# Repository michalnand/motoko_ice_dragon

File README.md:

# motoko ice dragon line follower

# source structure
- [3d_print](3d_print)
- [hardware](hardware)
- [simulations](simulations)
- [firmware](firmware)

# LQR controller 

## motor velocity control
- inner loop controls brushless motors
- LQR + Kalman are used for velocity control
- runs 4kHz

## position control
- outer loop controls robot state - distance and orientation
- LQR controller is used
- state is : (distance, orientation, velocity, angular rate)
- runs 250Hz

## LQR optimal control
- basic idea is solving discrete riccati algebraic equation
- to remove distrubance, integral action term is included

## motors velocity control
step response 1st order identification

- video of identification proces : https://www.youtube.com/watch?v=B-Wuzev6Ze0
- first the max RPM is estimated, using open loop and FOC controll
- during measuring max RPM the encoder noise variance is also measured (necessary for kalman filter)
- next step is calculating motor time constant (considering 1st order model)
- c++ source [identification.cpp](firmware/usr/identification.cpp#L16)
- LQR synthesis [lqg_discrete.ipynb](simulations/motor_controller/lqg_discrete.ipynb)
- step response and disturbance rejection

- controller for brushless motors in c++ (1D LQR + kalman) :
[lqg_single.cpp](firmware/LibsDrivers/lqg_single.cpp)

- whole motor driver : 
[motor_control.cpp](firmware/LibsDrivers/motor_control.cpp)

## position controll

- kalman based identification
- LQR synthesis
- [controller identification + synthetis](simulations/position_controller/position_controller_lqr.ipynb)
- step response and disturbance rejection

# photos

- [photos](doc/images/README.md)

- brushless motors
- LQG - linear quadratic regulator + Kalman filter
- LSTM for line shape prediction
- multiple local optimal LQR controllers selecting

# software architecture

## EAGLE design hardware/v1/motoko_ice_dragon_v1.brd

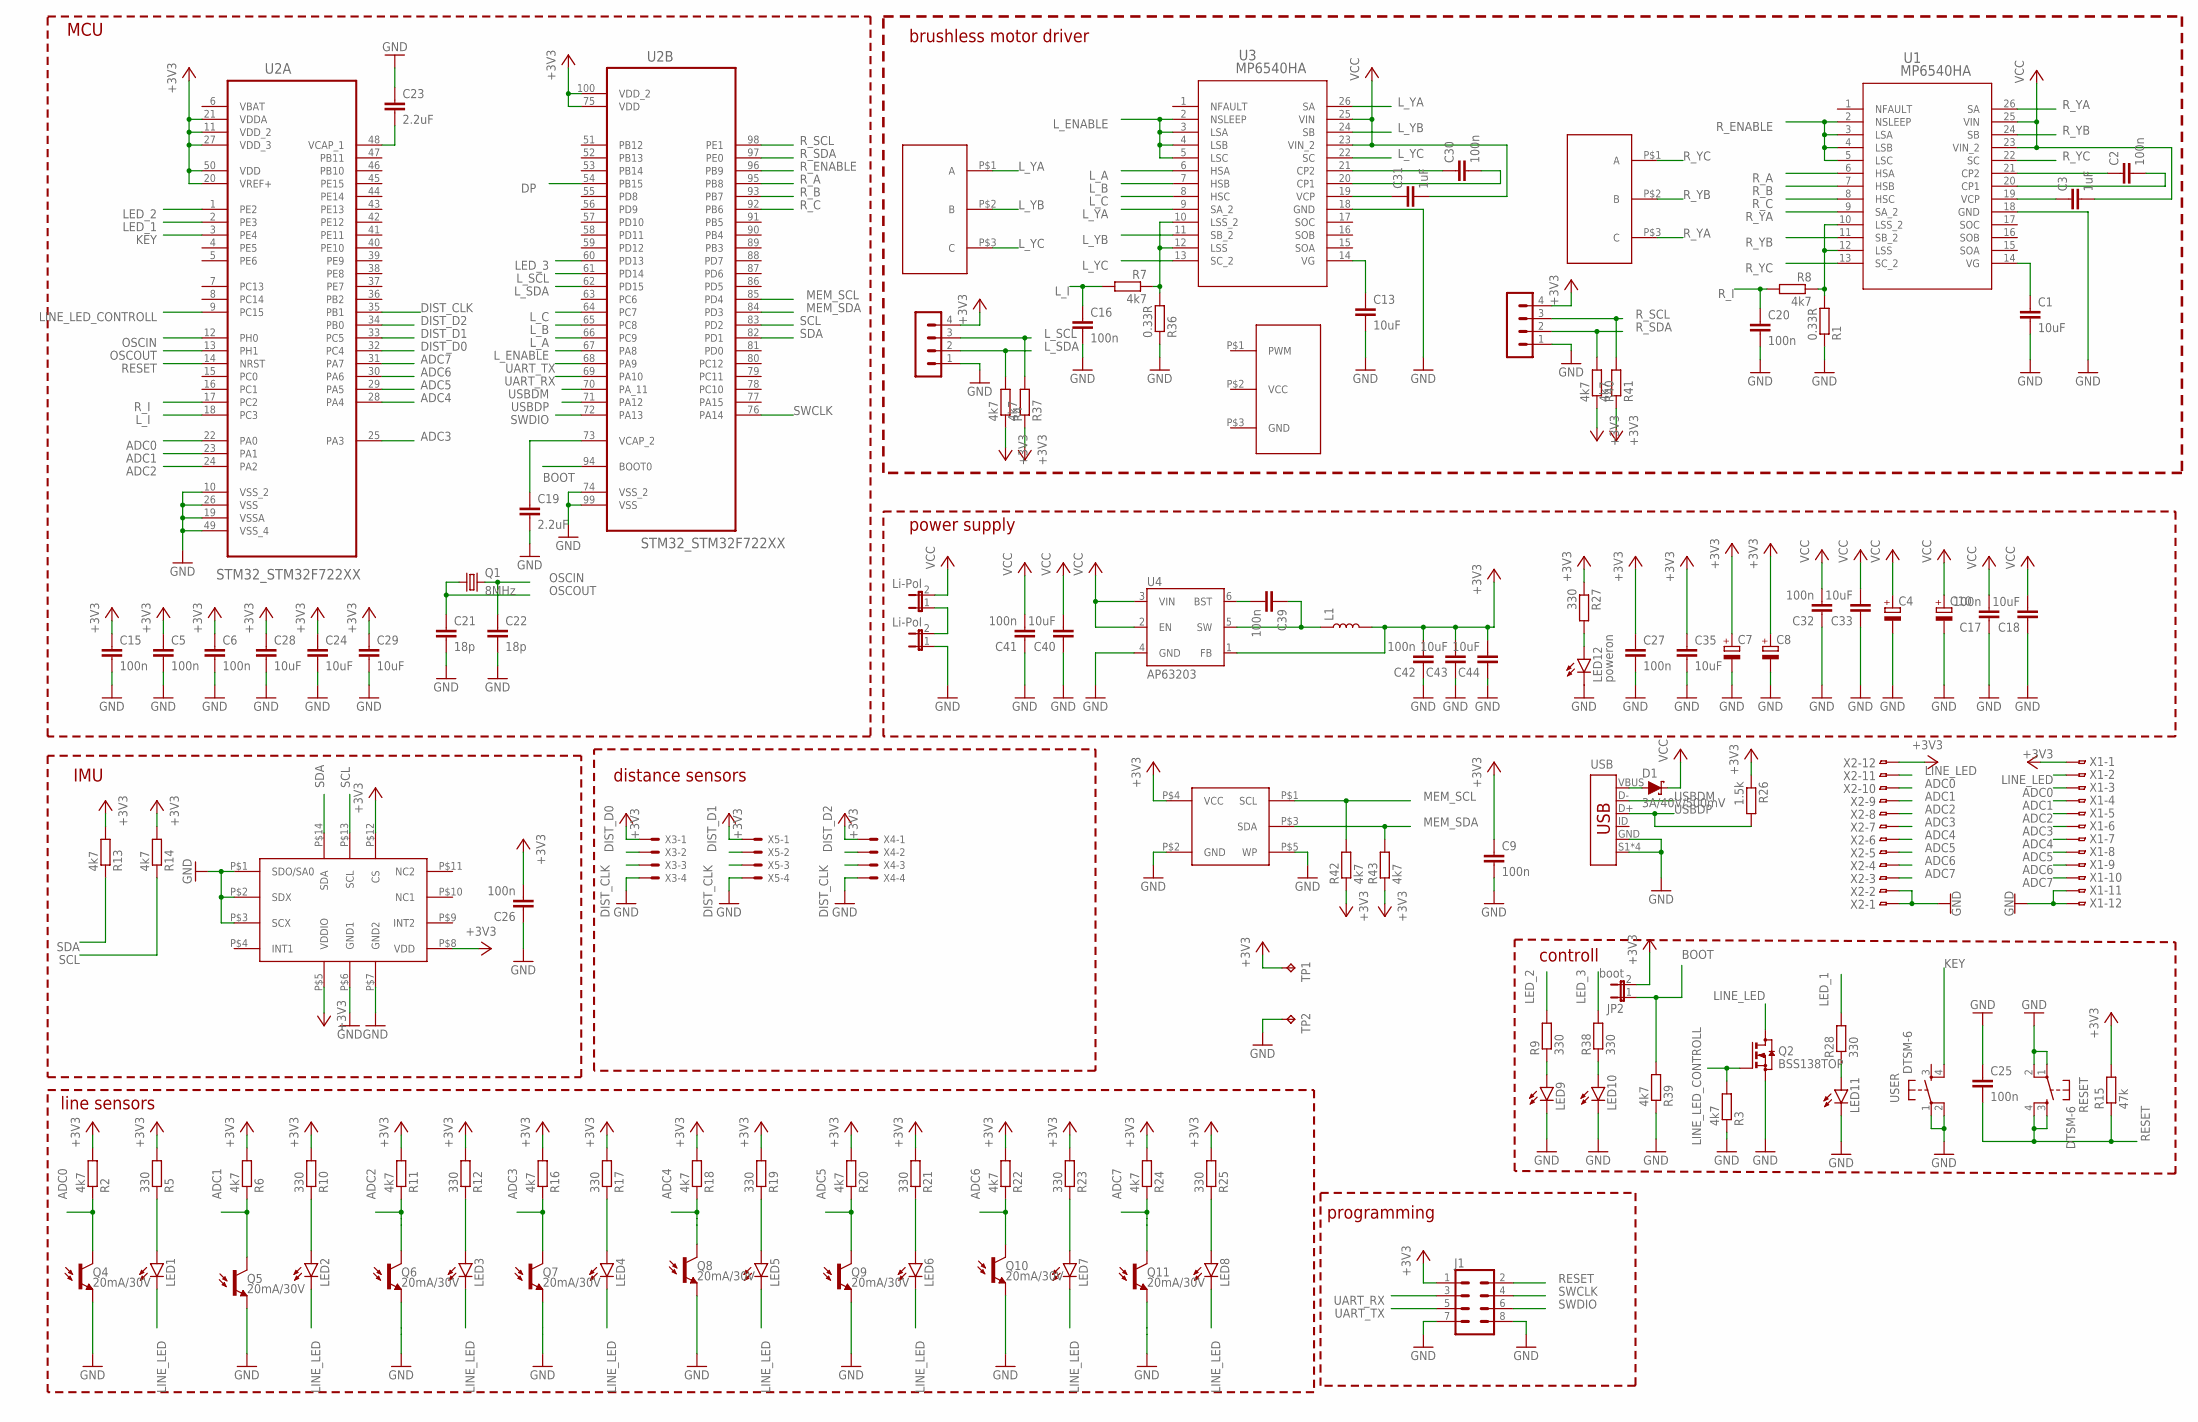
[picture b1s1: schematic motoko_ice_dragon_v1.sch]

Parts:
C1, C13, C18, C24, C28, C29, C33, C35, C40, C43, C44: 10uF; C0805
C2, C5, C6, C9, C15, C16, C17, C20, C25, C26, C27, C30, C32, C39, C41, C42: 100n; C0805
C3, C31: 1uF; C0805
C4, C7, C8, C10: CPOL-EU085CS-1AR; 085CS_1AR
C19, C23: 2.2uF; C0805
C21, C22: 18p; C0805
D1: 3A/40V/500mV; SMA-DIODE
J1: CONN_04X2; 2X4
JP1, JP3: Li-Pol; JP1
JP2: boot; JP1
L1: 4.7uH, TYS50204R7N-10; CR54
LED1, LED2, LED3, LED4, LED5, LED6, LED7, LED8, LED9, LED10, LED11: LEDCHIPLED_1206; CHIPLED_1206
LED12: poweron; CHIPLED_1206
L_ENCODER, L_ENCODER1: MA04-1
Q1: 8MHz; CTS406
Q2: BSS138TOP; SOT23
Q4, Q5, Q6, Q7, Q8, Q9, Q10, Q11: 20mA/30V; PT17-21C-L41-TR8
R1, R36: 0.33R; M1206
R2, R3, R4, R6, R7, R8, R11, R13, R14, R16, R18, R20, R22, R24, R37, R39, R40, R41, R42, R43: 4k7; M0805
R5, R9, R10, R12, R17, R19, R21, R23, R25, R27, R28, R38: 330; M0805
R15: 47k; M0805
R26: 1.5k; M0805
RESET: DTSM-6
TP1, TP2: TPB1,27; B1,27
U1, U3: MP6540HA; QFN-5X5_MP6540HA_MNP
U2: STM32_STM32F722XX; STM32_QFP50P1600X1600X160-100N
U4: AP63203; SOT23-6
U$1, U$2: BRUSHLESS_MOTOR_WHEEL
U$3: LSM6DSM; LGA14L
U$4: 24LC24_SOT23; SOT23
U$5: DUCTED_FAN_35MM
USB: USB_MINI-B_SMT; USB-MINIB
USER: DTSM-6
X1, X2: FH12-12S-0.5SH
X3, X4, X5: 52745-0490

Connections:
+3V3: C5.1, C6.1, C7.+, C8.+, C9.1, C15.1, C24.1, C26.2, C27.1, C28.1, C29.1, C35.1, C42.2, C43.2, C44.2, J1.1, JP2.2, L1.P$2 (2), L_ENCODER.4, L_ENCODER1.4, R2.2, R4.1, R5.2, R6.2, R10.2, R11.2, R12.2, R13.2, R14.2, R15.2, R16.2, R17.2, R18.2, R19.2, R20.2, R21.2, R22.2, R23.2, R24.2, R25.2, R26.1, R27.1, R37.1, R40.1, R41.1, R42.1, R43.1, TP1.TP, U2.11 (VDD_2), U2.20 (VREF+), U2.21 (VDDA), U2.27 (VDD_3), U2.50 (VDD), U2.75 (VDD), U2.100 (VDD_2), U4.1 (FB), U$3.P$5 (VDDIO), U$3.P$8 (VDD), U$3.P$12 (CS), U$4.P$4 (VCC), X1.1, X2.12, X3.1, X4.1, X5.1
ADC0: Q4.C, R2.1, U2.22 (PA0), X1.3, X2.10
ADC1: Q5.C, R6.1, U2.23 (PA1), X1.4, X2.9
ADC2: Q6.C, R11.1, U2.24 (PA2), X1.5, X2.8
ADC3: Q7.C, R16.1, U2.25 (PA3), X1.6, X2.7
ADC4: Q8.C, R18.1, U2.28 (PA4), X1.7, X2.6
ADC5: Q9.C, R20.1, U2.29 (PA5), X1.8, X2.5
ADC6: Q10.C, R22.1, U2.30 (PA6), X1.9, X2.4
ADC7: Q11.C, R24.1, U2.31 (PA7), X1.10, X2.3
BOOT: JP2.1, R39.2, U2.94 (BOOT0)
DIST_CLK: U2.35 (PB1), X3.3, X4.3, X5.3
DIST_D0: U2.32 (PC4), X3.2
DIST_D1: U2.33 (PC5), X5.2
DIST_D2: U2.34 (PB0), X4.2
DP: U2.54 (PB15)
GND: C1.2, C4.-, C5.2, C6.2, C7.-, C8.-, C9.2, C10.-, C13.2, C15.2, C16.2, C17.1, C18.1, C19.2, C20.2, C21.2, C22.2, C23.1, C24.2, C25.1, C26.1, C27.2, C28.2, C29.2, C32.1, C33.1, C35.2, C40.1, C41.1, C42.1, C43.1, C44.1, J1.7, J1.8, JP3.1, LED9.C, LED10.C, LED11.C, LED12.C, L_ENCODER.1, L_ENCODER1.1, Q2.2 (S), Q4.E, Q5.E, Q6.E, Q7.E, Q8.E, Q9.E, Q10.E, Q11.E, R1.1, R3.1, R36.1, R39.1, RESET.1, RESET.2, TP2.TP, U1.18 (GND), U2.10 (VSS_2), U2.19 (VSSA), U2.26 (VSS), U2.49 (VSS_4), U2.74 (VSS_2), U2.99 (VSS), U3.18 (GND), U4.4 (GND), U$3.P$1 (SDO/SA0), U$3.P$2 (SDX), U$3.P$3 (SCX), U$3.P$6 (GND1), U$3.P$7 (GND2), U$4.P$2 (GND), U$4.P$5 (WP), USB.GND, USB.S1 (SHIELD), USB.S2 (SHIELD), USB.S3 (SHIELD), USB.S4 (SHIELD), USER.1, USER.2, X1.11, X1.12, X2.1, X2.2, X3.4, X4.4, X5.4
KEY: U2.3 (PE4), USER.4
LED_1: R28.2, U2.2 (PE3)
LED_2: R9.2, U2.1 (PE2)
LED_3: R38.2, U2.60 (PD13)
LINE_LED: LED1.C, LED2.C, LED3.C, LED4.C, LED5.C, LED6.C, LED7.C, LED8.C, Q2.3 (D), X1.2, X2.11
LINE_LED_CONTROLL: Q2.1 (G), R3.2, U2.9 (PC15)
L_A: U2.66 (PC9), U3.6 (HSA)
L_B: U2.65 (PC8), U3.7 (HSB)
L_C: U2.64 (PC7), U3.8 (HSC)
L_ENABLE: U2.67 (PA8), U3.2 (NSLEEP), U3.3 (LSA), U3.4 (LSB), U3.5 (LSC)
L_I: C16.1, R7.2, U2.18 (PC3)
L_SCL: L_ENCODER.3, R37.2, U2.61 (PD14)
L_SDA: L_ENCODER.2, R4.2, U2.62 (PD15)
L_YA: U3.9 (SA_2), U3.26 (SA), U$1.P$1 (A)
L_YB: U3.11 (SB_2), U3.24 (SB), U$1.P$2 (B)
L_YC: U3.13 (SC_2), U3.22 (SC), U$1.P$3 (C)
MEM_SCL: R42.2, U2.85 (PD4), U$4.P$1 (SCL)
MEM_SDA: R43.2, U2.84 (PD3), U$4.P$3 (SDA)
unnamed: R7.1, R36.2, U3.10 (LSS_2), U3.12 (LSS)
unnamed: C1.1, U1.14 (VG)
unnamed: C2.1, U1.21 (CP2)
unnamed: C2.2, U1.20 (CP1)
unnamed: C3.1, U1.19 (VCP)
unnamed: D1.A, USB.VBUS
unnamed: JP1.1, JP3.2
unnamed: R1.2, R8.1, U1.10 (LSS_2), U1.12 (LSS)
unnamed: LED9.A, R9.1
unnamed: C13.1, U3.14 (VG)
unnamed: LED10.A, R38.1
unnamed: C31.1, U3.19 (VCP)
unnamed: LED1.A, R5.1
unnamed: LED2.A, R10.1
unnamed: LED3.A, R12.1
unnamed: LED4.A, R17.1
unnamed: LED5.A, R19.1
unnamed: LED6.A, R21.1
unnamed: LED7.A, R23.1
unnamed: LED8.A, R25.1
unnamed: C39.2, U4.6 (BST)
unnamed: LED12.A, R27.2
unnamed: C19.1, U2.73 (VCAP_2)
unnamed: C39.1, L1.P$1 (1), U4.5 (SW)
unnamed: C23.2, U2.48 (VCAP_1)
unnamed: C30.1, U3.21 (CP2)
unnamed: LED11.A, R28.1
unnamed: C30.2, U3.20 (CP1)
OSCIN: C22.1, Q1.3 (2), U2.12 (PH0)
OSCOUT: C21.1, Q1.1, U2.13 (PH1)
RESET: C25.2, J1.2, R15.1, RESET.3, RESET.4, U2.14 (NRST)
R_A: U1.6 (HSA), U2.95 (PB8)
R_B: U1.7 (HSB), U2.93 (PB7)
R_C: U1.8 (HSC), U2.92 (PB6)
R_ENABLE: U1.2 (NSLEEP), U1.3 (LSA), U1.4 (LSB), U1.5 (LSC), U2.96 (PB9)
R_I: C20.1, R8.2, U2.17 (PC2)
R_SCL: L_ENCODER1.3, R41.2, U2.98 (PE1)
R_SDA: L_ENCODER1.2, R40.2, U2.97 (PE0)
R_YA: U1.9 (SA_2), U1.26 (SA), U$2.P$3 (C)
R_YB: U1.11 (SB_2), U1.24 (SB), U$2.P$2 (B)
R_YC: U1.13 (SC_2), U1.22 (SC), U$2.P$1 (A)
SCL: R14.1, U2.83 (PD2), U$3.P$13 (SCL)
SDA: R13.1, U2.82 (PD1), U$3.P$14 (SDA)
SWCLK: J1.4, U2.76 (PA14)
SWDIO: J1.6, U2.72 (PA13)
UART_RX: J1.3, U2.69 (PA10)
UART_TX: J1.5, U2.68 (PA9)
USBDM: U2.70 (PA_11), USB.D-
USBDP: R26.2, U2.71 (PA12), USB.D+
VBAT: U2.6 (VBAT)
VCC: C3.2, C4.+, C10.+, C17.2, C18.2, C31.2, C32.2, C33.2, C40.2, C41.2, D1.C, JP1.2, U1.23 (VIN_2), U1.25 (VIN), U3.23 (VIN_2), U3.25 (VIN), U4.2 (EN), U4.3 (VIN)

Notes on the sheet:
power supply
line sensors
programming
MCU
distance sensors
controll
IMU
brushless motor driver

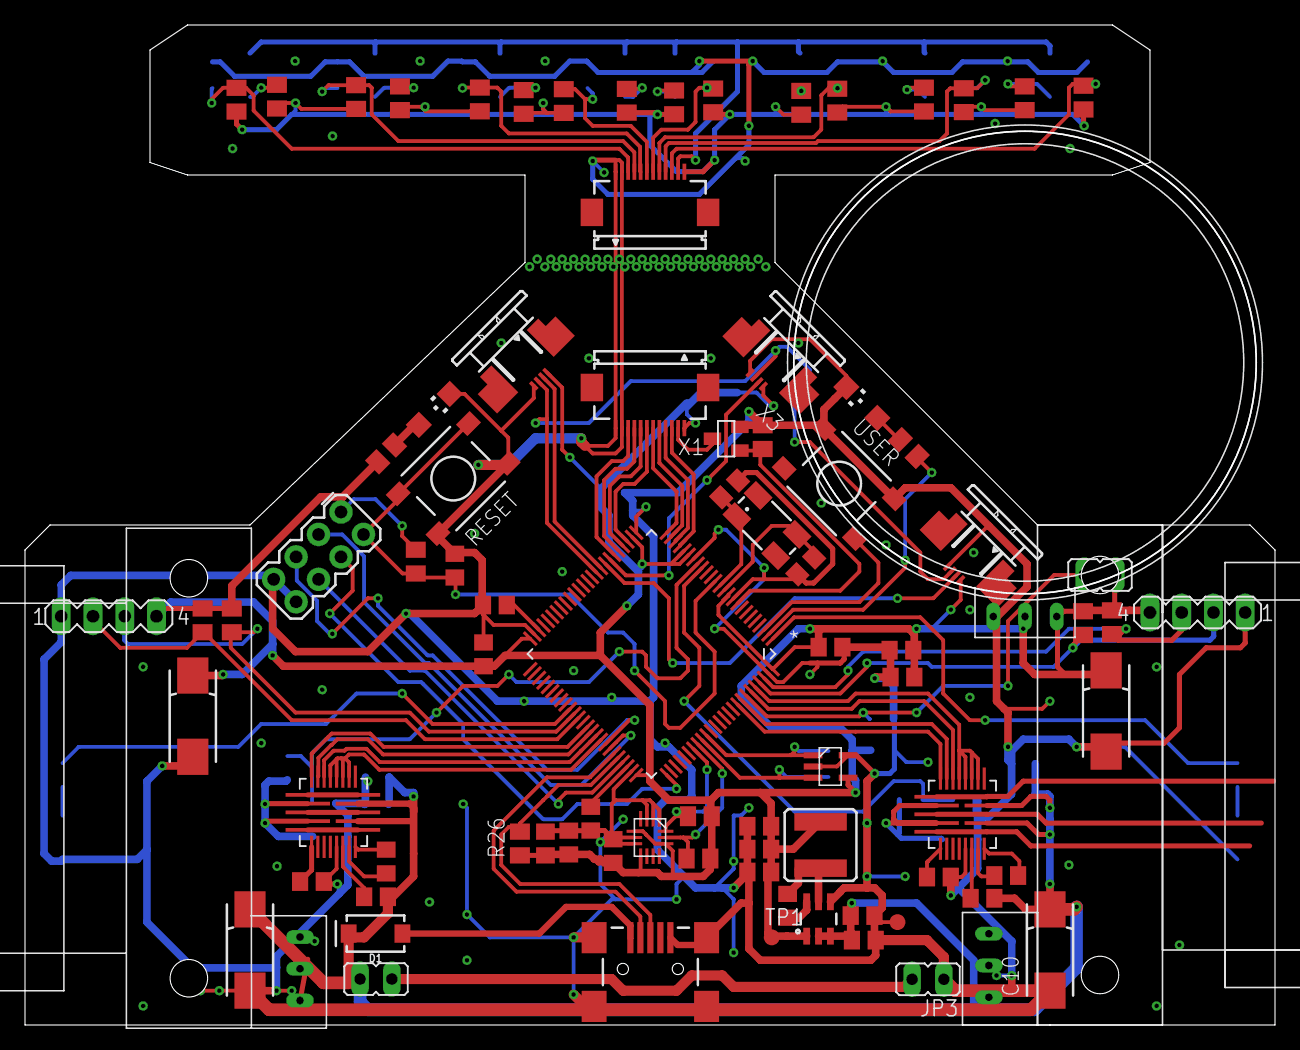
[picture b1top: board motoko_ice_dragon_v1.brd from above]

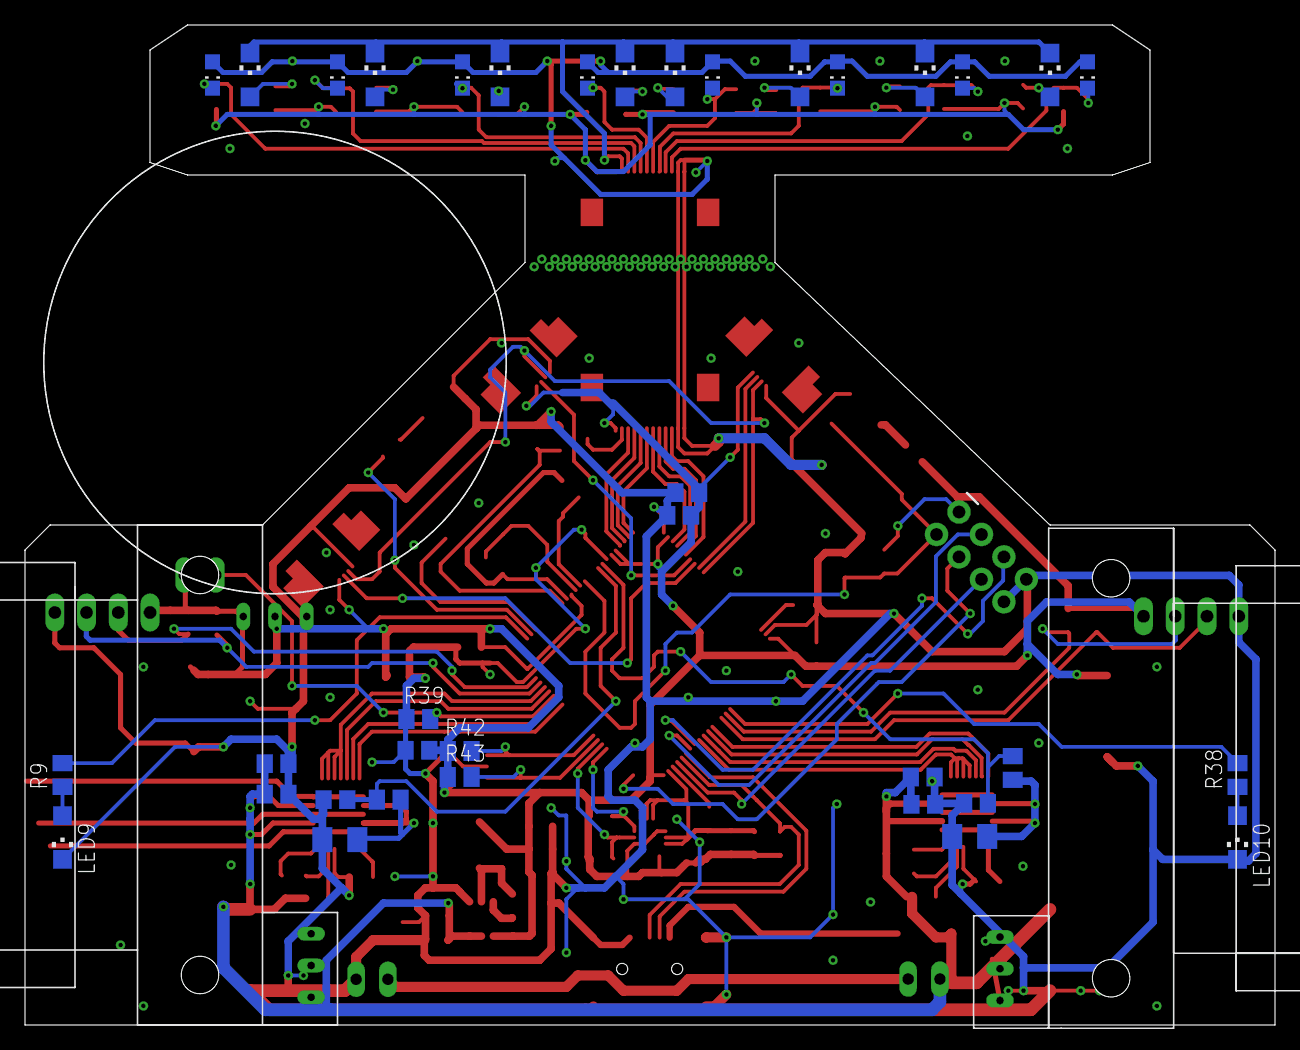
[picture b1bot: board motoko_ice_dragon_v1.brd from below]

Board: 2 copper layers, 100.0 x 80.0 mm, 122 parts (37 on the bottom side), 83 nets.

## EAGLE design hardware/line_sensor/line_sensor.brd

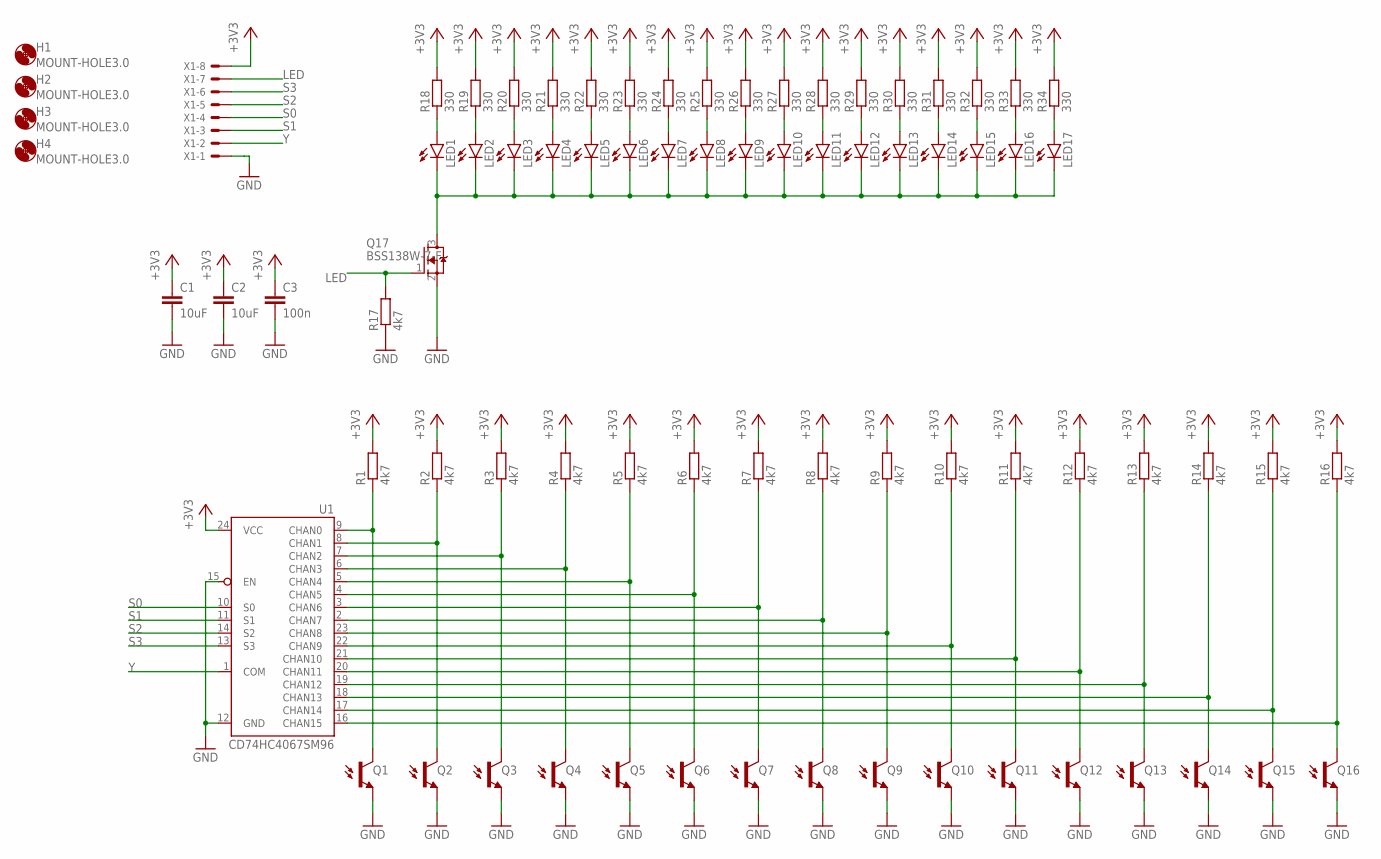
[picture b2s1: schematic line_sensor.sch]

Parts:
C1, C2: 10uF; C0805
C3: 100n; C0805
H1, H2, H3, H4: MOUNT-HOLE3.0; 3,0
LED1, LED2, LED3, LED4, LED5, LED6, LED7, LED8, LED9, LED10, LED11, LED12, LED13, LED14, LED15, LED16, LED17: LEDSML1206; SML1206
Q1, Q2, Q3, Q4, Q5, Q6, Q7, Q8, Q9, Q10, Q11, Q12, Q13, Q14, Q15, Q16: 20mA/30V; PT17-21C-L41-TR8
Q17: BSS138W-7-F; SOT323
R1, R2, R3, R4, R5, R6, R7, R8, R9, R10, R11, R12, R13, R14, R15, R16, R17: 4k7; M0805
R18, R19, R20, R21, R22, R23, R24, R25, R26, R27, R28, R29, R30, R31, R32, R33, R34: 330; M0805
U1: CD74HC4067SM96; SSOP24
X1: 52745-0890

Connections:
+3V3: C1.1, C2.1, C3.1, R1.2, R2.2, R3.2, R4.2, R5.2, R6.2, R7.2, R8.2, R9.2, R10.2, R11.2, R12.2, R13.2, R14.2, R15.2, R16.2, R18.2, R19.2, R20.2, R21.2, R22.2, R23.2, R24.2, R25.2, R26.2, R27.2, R28.2, R29.2, R30.2, R31.2, R32.2, R33.2, R34.2, U1.24 (VCC), X1.8
GND: C1.2, C2.2, C3.2, Q1.E, Q2.E, Q3.E, Q4.E, Q5.E, Q6.E, Q7.E, Q8.E, Q9.E, Q10.E, Q11.E, Q12.E, Q13.E, Q14.E, Q15.E, Q16.E, Q17.2 (S), R17.1, U1.12 (GND), U1.15 (EN), X1.1
LED: Q17.1 (G), R17.2, X1.7
unnamed: Q2.C, R2.1, U1.8 (CHAN1)
unnamed: Q1.C, R1.1, U1.9 (CHAN0)
unnamed: Q3.C, R3.1, U1.7 (CHAN2)
unnamed: Q4.C, R4.1, U1.6 (CHAN3)
unnamed: LED1.A, R18.1
unnamed: LED2.A, R19.1
unnamed: LED1.C, LED2.C, LED3.C, LED4.C, LED5.C, LED6.C, LED7.C, LED8.C, LED9.C, LED10.C, LED11.C, LED12.C, LED13.C, LED14.C, LED15.C, LED16.C, LED17.C, Q17.3 (D)
unnamed: Q5.C, R5.1, U1.5 (CHAN4)
unnamed: Q6.C, R6.1, U1.4 (CHAN5)
unnamed: Q7.C, R7.1, U1.3 (CHAN6)
unnamed: Q8.C, R8.1, U1.2 (CHAN7)
unnamed: Q9.C, R9.1, U1.23 (CHAN8)
unnamed: Q10.C, R10.1, U1.22 (CHAN9)
unnamed: Q11.C, R11.1, U1.21 (CHAN10)
unnamed: Q12.C, R12.1, U1.20 (CHAN11)
unnamed: Q13.C, R13.1, U1.19 (CHAN12)
unnamed: Q14.C, R14.1, U1.18 (CHAN13)
unnamed: Q15.C, R15.1, U1.17 (CHAN14)
unnamed: Q16.C, R16.1, U1.16 (CHAN15)
unnamed: LED3.A, R20.1
unnamed: LED4.A, R21.1
unnamed: LED5.A, R22.1
unnamed: LED6.A, R23.1
unnamed: LED7.A, R24.1
unnamed: LED8.A, R25.1
unnamed: LED9.A, R26.1
unnamed: LED10.A, R27.1
unnamed: LED11.A, R28.1
unnamed: LED12.A, R29.1
unnamed: LED13.A, R30.1
unnamed: LED14.A, R31.1
unnamed: LED15.A, R32.1
unnamed: LED16.A, R33.1
unnamed: LED17.A, R34.1
S0: U1.10 (S0), X1.4
S1: U1.11 (S1), X1.3
S2: U1.14 (S2), X1.5
S3: U1.13 (S3), X1.6
Y: U1.1 (COM), X1.2

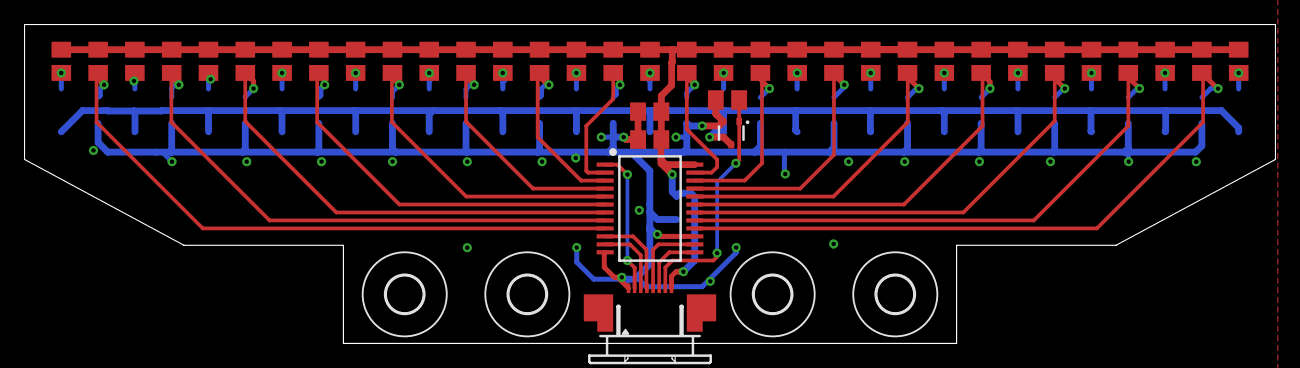
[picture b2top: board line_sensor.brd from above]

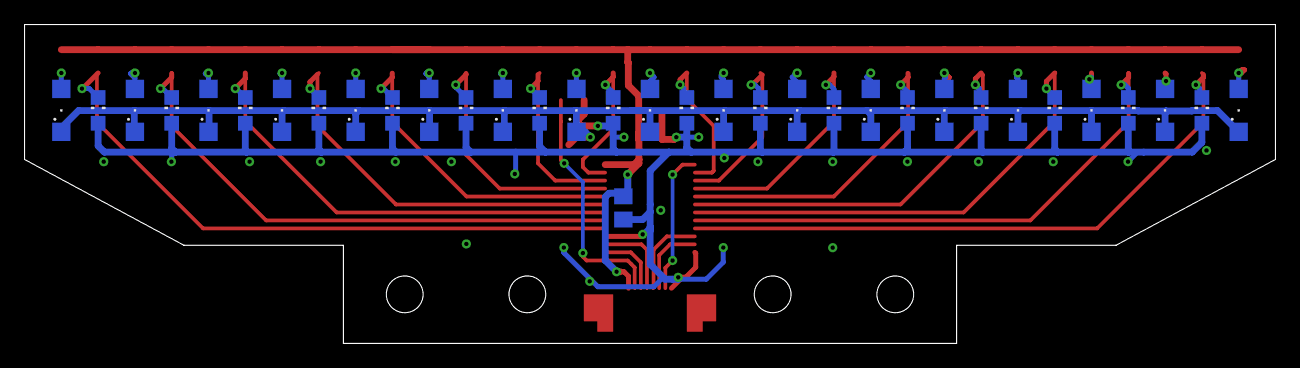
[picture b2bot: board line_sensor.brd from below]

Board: 2 copper layers, 102.0 x 26.0 mm, 77 parts (34 on the bottom side), 42 nets.

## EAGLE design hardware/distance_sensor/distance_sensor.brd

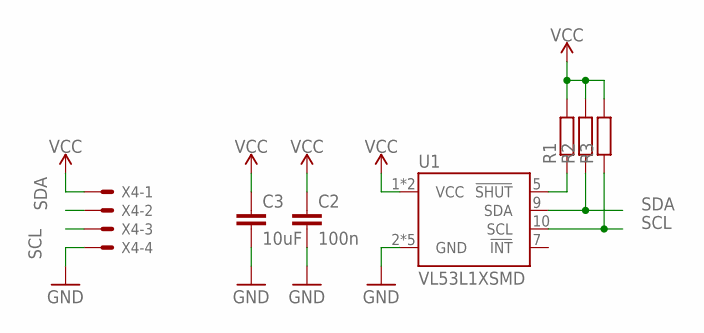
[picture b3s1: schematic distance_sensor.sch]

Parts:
C2: 100n; C0805
C3: 10uF; C0805
R1, R2, R3: R-EU_M0805; M0805
U1: VL53L1XSMD; VL53L1X
X4: 52745-0490

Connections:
GND: C2.2, C3.2, U1.2 (GND), U1.3 (GND), U1.4 (GND), U1.6 (GND), U1.12 (GND), X4.4
unnamed: R1.1, U1.5 (!SHUT)
SCL: R3.1, U1.10 (SCL), X4.3
SDA: R2.1, U1.9 (SDA), X4.2
VCC: C2.1, C3.1, R1.2, R2.2, R3.2, U1.1 (VCC), U1.11 (VCC), X4.1

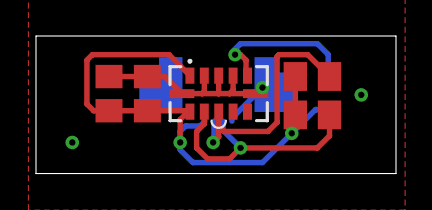
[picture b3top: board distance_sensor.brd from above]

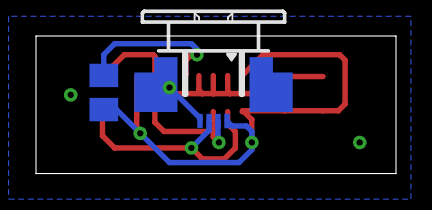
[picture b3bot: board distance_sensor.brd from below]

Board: 2 copper layers, 20.0 x 7.6 mm, 7 parts (2 on the bottom side), 5 nets.

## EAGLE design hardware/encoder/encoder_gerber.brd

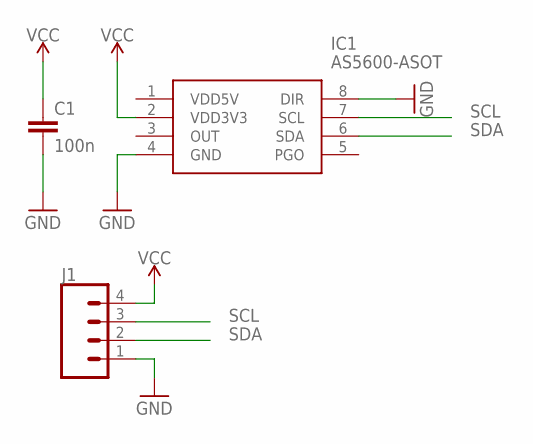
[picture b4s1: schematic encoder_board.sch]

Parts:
C1: 100n; C0805
IC1: AS5600-ASOT; SOIC127P600X175-8N
J1: CONN_04LONGPADS; 1X04_LONGPADS

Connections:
GND: C1.2, IC1.4 (GND), IC1.8 (DIR), J1.1
SCL: IC1.7 (SCL), J1.3
SDA: IC1.6 (SDA), J1.2
VCC: C1.1, IC1.2 (VDD3V3), J1.4

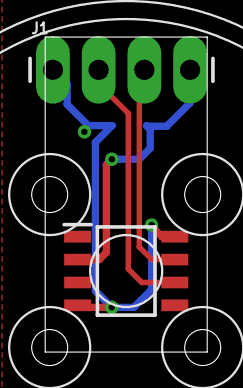
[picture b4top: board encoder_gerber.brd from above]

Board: 2 copper layers, 9.0 x 17.5 mm, 4 parts (1 on the bottom side), 4 nets.

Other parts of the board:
U$1: BRUSHLESS_GIMBAL_MOTOR_2204

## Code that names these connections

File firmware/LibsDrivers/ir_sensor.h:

#ifndef _IR_SENSOR_H_
#define _IR_SENSOR_H_

#include <gpio.h>
#include <biquad_filter.h>

#define IR_SENSORS_COUNT        ((unsigned int)4)


/*
    IR left         :   PB1     ADC1, ADC2, IN9
    IR front left   :   PC5     ADC1, ADC2, IN15
    IR front right  :   PC4     ADC1, ADC2, IN14
    IR right        :   PB0     ADC1, ADC2, IN8
*/

class IRSensor
{
    public:
        void init();

        void callback();

        float* get();

        int obstacle_detected();


        void print();
    
    private:
        float calibration(float *callibration, float x);

    public:
        uint32_t measurement_id;

    private: 
        uint32_t state;
        Gpio<TGPIOC, 14, GPIO_MODE_OUT> ir_led;         //ir led
  

        int ir_off[IR_SENSORS_COUNT];
        int ir_on[IR_SENSORS_COUNT];

        float filter_coeff;
        

    private:
        float distance[IR_SENSORS_COUNT];

};

#endif

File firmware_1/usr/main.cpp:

#include "device.h"
#include <drivers.h>
#include <tests.h>

#include <identification.h>
#include <line_following.h>

//#include <position_control_lqr.h>
#include <position_control_lqg.h>
#include <trajectory_tracking.h>

#include <fmath.h>

 
#define LED_1_GPIO        TGPIOE
#define LED_1_PIN         3
 
#define LED_2_GPIO        TGPIOE 
#define LED_2_PIN         2   

#define LED_3_GPIO        TGPIOD 
#define LED_3_PIN         13

#define KEY_GPIO          TGPIOE 
#define KEY_PIN           4 

#include <gonio.h>

int main(void)      
{ 
  drivers_init();
  
  //main LQR controller init
  //position_control.init();  

  //LineFollowing line_following;

  terminal << "\n\n\n"; 
  terminal << "machine ready\n";
  

  Gpio<LED_1_GPIO, LED_1_PIN, GPIO_MODE_OUT> led_1;   //user led
  led_1 = 1;  

  Gpio<LED_2_GPIO, LED_2_PIN, GPIO_MODE_OUT> led_2;   //bottom led
  Gpio<LED_3_GPIO, LED_3_PIN, GPIO_MODE_OUT> led_3;   //bottom led
    
  Gpio<KEY_GPIO, KEY_PIN, GPIO_MODE_IN_PULLUP> key;   //user button
 
  for (unsigned int i = 0; i < 5; i++)
  {     
    led_2 = 1;  
    led_3 = 1; 
    timer.delay_ms(50);
 
    led_2 = 0; 
    led_3 = 0; 
    timer.delay_ms(100);
  }

  led_2 = 1; 
  led_3 = 1;  


  while (key != 0)
  { 
    led_1 = 1; 
    timer.delay_ms(100);

    led_1 = 0; 
    timer.delay_ms(200);
  }
  
  led_1 = 1; 

  while (key == 0)
  {
    led_1 = 1; 
    timer.delay_ms(50);

    led_1 = 0; 
    timer.delay_ms(50);
  } 

  led_1 = 1; 

  timer.delay_ms(1500);

  //mcu_usage();
  //noise_measurement();

  //timer_test();

  //left_motor_connect_test();
  //right_motor_connect_test();

  //ir_sensor_test();
  //line_sensor_test();
  //gyro_sensor_test(); 
  //encoder_sensor_test();
  //sensors_test();
  

  //left_motor_pwm_test();
  //right_motor_pwm_test();
  //encoder_sensor_test();

  //motor_identification();
  //motor_driver_test();   
  //shaper_test();
  
  robot_dynamics_identification();


  //line_following.main(); 
  
  //line_following.obstacle_avoid();
  //line_following.line_search(LINE_LOST_CENTER);
  
  

  while (1) 
  {
    led_1 = 1; 
    timer.delay_ms(100);

    led_1 = 0; 
    timer.delay_ms(100);

    led_1 = 1; 
    timer.delay_ms(200);

    led_1 = 0; 
    timer.delay_ms(400);
  }
 
  return 0;
} 

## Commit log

2023-04-25 initial
2023-04-26 lqr design
2023-06-08 lqr controller
2023-06-08 visualisation
2023-06-11 main board
2023-06-15 lqr control
2023-06-19 doc + photos + 3d parts
2023-06-20 initial firmware
2023-06-20 firmware drivers
2023-06-24 running sensors + calibration, motors work in progress
2023-06-24 motor foc
2023-06-26 identification
2023-06-28 optimised code
2023-06-29 lqr cpp implementation
2023-06-29 lqr position control
2023-07-01 identification, sensors calibrations
2023-07-03 line following
2023-07-05 board rev 2
2023-07-16 gyro tests
2023-07-18 gyro test, velocity LQR
2023-07-22 tuned velocity controller
2023-11-25 simulations, controller experiments
2024-02-03 new board
2024-02-04 boards
2024-02-10 motor controll + kalman
2024-02-12 shaper for motor control
2024-02-12 lqg controller
2024-02-16 controller
2024-02-17 robot identification
2024-02-17 lqr positional control
2024-02-19 optimal control
2024-02-22 line following, lqr, shaper
2024-02-27 curve motion, line following
2024-03-01 faster line following
2024-03-03 code clean up
2024-03-04 line search
2024-03-05 documentation
2024-03-08 optimizations
2024-03-08 split line detection
2024-03-28 ir calibration polynoms
2024-03-29 obstacle avoiding, first tests
2024-04-02 brick avoiding
2024-04-03 obstacle avoiding
2024-04-18 working version
2024-04-21 line sensor fixed, faster reading + low pass filter added
2024-05-29 new foc

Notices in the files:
parts and their libraries:
SparkFun-Sensors: Licensing: Creative Commons ShareAlike 4.0 International - https://creativecommons.org/licenses/by-sa/4.0
COPYRIGHT: Copyright (C) 2018 Accelerated Designs. All rights reserved
